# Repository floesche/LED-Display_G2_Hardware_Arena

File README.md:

---
title: Arena PCBs
parent: Generation 2
---

## Project content

```
├── arena_12_20
│   ├── gerber_v1
│   ├── gerber_v2
│   ├── pdf
│   └── svg
├── arena_12_20_top
│   └── gerber_v1
├── arena_mini
│   ├── gerber_v1
│   └── pdf
├── full
│   ├── 12-ring
│   └── 24-ring
├── mod
├── pdfs
├── planar_arena_8x
│   └── gerber_v0p1
└── planar_arena_8x_base
    ├── v0p1
    └── v0p2
```

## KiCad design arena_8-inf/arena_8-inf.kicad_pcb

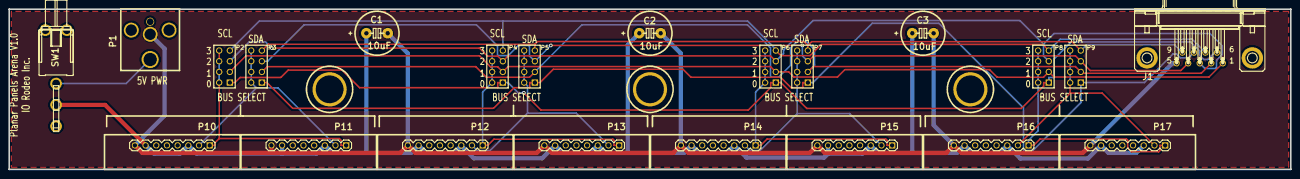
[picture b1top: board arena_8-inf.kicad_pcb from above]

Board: 2 copper layers, 304.8 x 38.1 mm, 25 parts (0 on the bottom side), 19 nets.

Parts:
C1, C2, C3: 10uF; JFRC_Capacitor_Polarized
J1: DB9; DB9_M09
M1, M2, M3: 1%2f4-20
P1: CONN_2; DCJACK_2PIN_HIGHCURRENT
P2, P3, P4, P5, P6, P7, P8, P9: CONN_4X2; pin_array_4x2
P10, P11, P12, P13, P14, P15, P16, P17: CONN_8; PANEL_RT_ANG_INV
SW1: SWITCH_INV; JFRC_LPV-1

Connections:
/5V: C1.1, C2.1, C3.1, P10.3, P10.7, P11.3, P11.7, P12.3, P12.7, P13.3, P13.7, P14.3, P14.7, P15.3, P15.7, P16.3, P16.7, P17.3, P17.7, SW1.2
/SCL0: J1.6, P2.1, P4.1, P6.1, P8.1
/SCL1: J1.1, P2.3, P4.3, P6.3, P8.3
/SCL2: J1.3, P2.5, P4.5, P6.5, P8.5
/SCL3: J1.7, P2.7, P4.7, P6.7, P8.7
/SCL_A: P2.2, P2.4, P2.6, P2.8, P10.1, P11.1
/SCL_B: P4.2, P4.4, P4.6, P4.8, P12.1, P13.1
/SCL_C: P6.2, P6.4, P6.6, P6.8, P14.1, P15.1
/SCL_D: P8.2, P8.4, P8.6, P8.8, P16.1, P17.1
/SDA0: J1.8, P3.1, P5.1, P7.1, P9.1
/SDA1: J1.2, P3.3, P5.3, P7.3, P9.3
/SDA2: J1.4, P3.5, P5.5, P7.5, P9.5
/SDA3: J1.9, P3.7, P5.7, P7.7, P9.7
/SDA_A: P3.2, P3.4, P3.6, P3.8, P10.2, P11.2
/SDA_B: P5.2, P5.4, P5.6, P5.8, P12.2, P13.2
/SDA_C: P7.2, P7.4, P7.6, P7.8, P14.2, P15.2
/SDA_D: P9.2, P9.4, P9.6, P9.8, P16.2, P17.2
GND: C1.2, C2.2, C3.2, J1.5, P1.2, P10.8, P11.8, P12.8, P13.8, P14.8, P15.8, P16.8, P17.8
unnamed: P1.1, SW1.1

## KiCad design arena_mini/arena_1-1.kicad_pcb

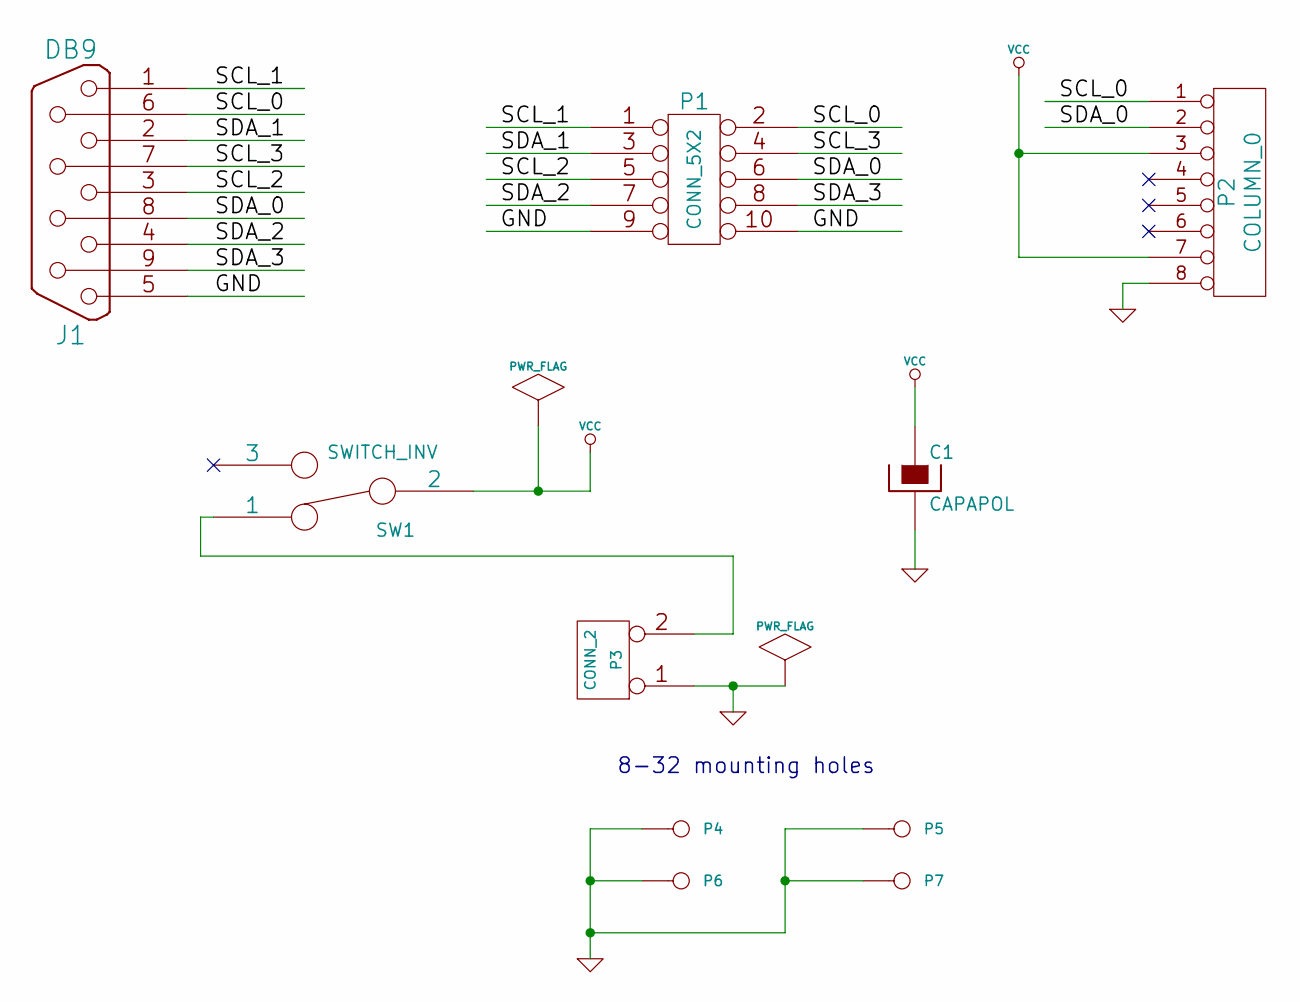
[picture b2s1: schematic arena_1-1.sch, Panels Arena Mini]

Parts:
C1: CAPAPOL
J1: DB9
P1: CONN_5X2
P2: COLUMN_0
P3: CONN_2
P4, P5, P6, P7: CONN_1
SW1: SWITCH_INV

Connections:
/GND: C1.2, J1.5, P1.9, P1.10, P2.8, P3.1, P4.1, P5.1, P6.1, P7.1
/SCL_0: J1.6, P1.2, P2.1
/SCL_1: J1.1, P1.1
/SCL_2: J1.3, P1.5
/SCL_3: J1.7, P1.4
/SDA_0: J1.8, P1.6, P2.2
/SDA_1: J1.2, P1.3
/SDA_2: J1.4, P1.7
/SDA_3: J1.9, P1.8
unnamed: P3.2 (PM), SW1.1
VCC: C1.1, P2.3, P2.7, SW1.2

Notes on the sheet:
8-32 mounting holes

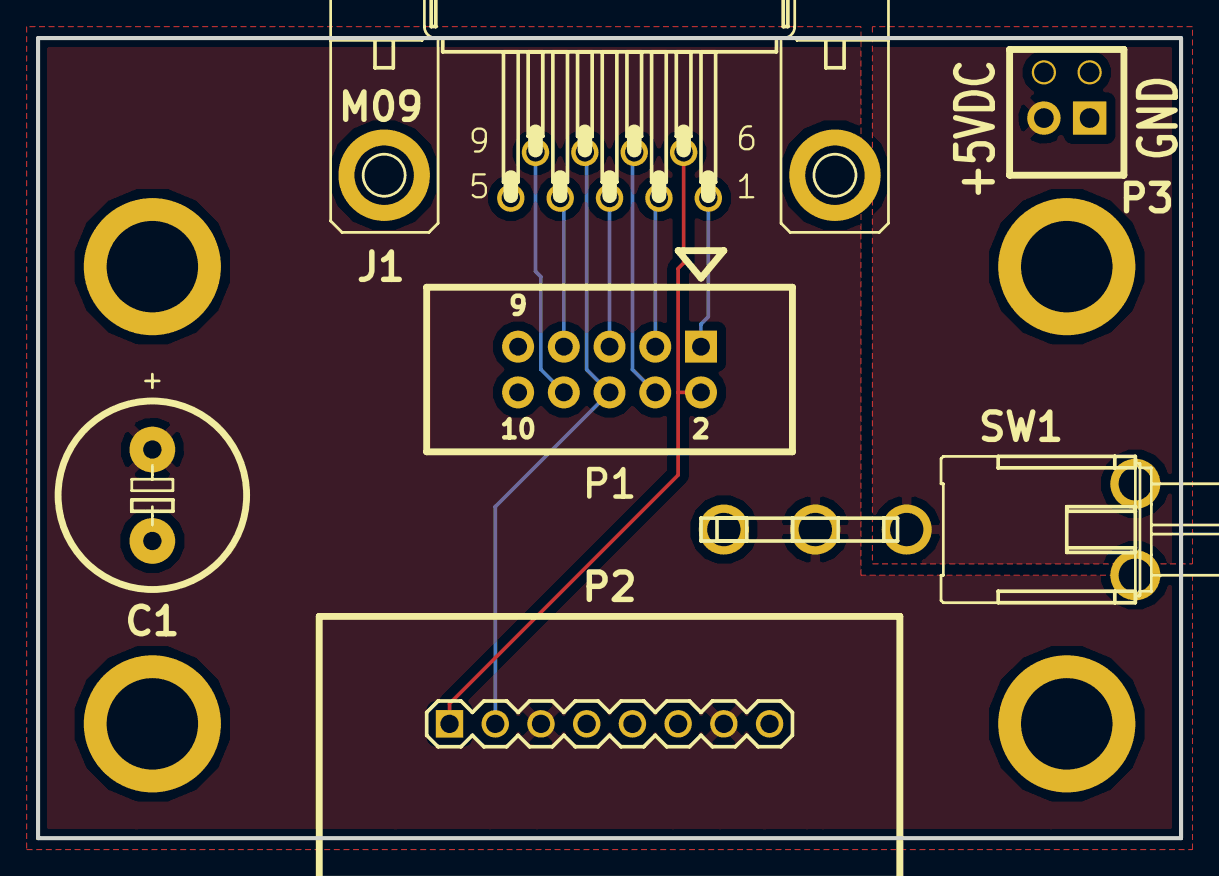
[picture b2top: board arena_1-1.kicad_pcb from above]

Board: 2 copper layers, 63.5 x 44.4 mm, 10 parts (0 on the bottom side), 11 nets.

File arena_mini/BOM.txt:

-*- mode:org -*-

# panels_arena_mini.lst
| ref | value      |
|-----+------------|
| C1  | CAPAPOL    |
| J1  | DB9        |
| P1  | CONN_5X2   |
| P2  | COLUMN_0   |
| P3  | CONN_2     |
| P4  | CONN_1     |
| P5  | CONN_1     |
| P6  | CONN_1     |
| P7  | CONN_1     |
| SW1 | SWITCH_INV |

# Bill of Materials
| ! | part  | description                                               | vendor       | part number   | quantity |  cost |
|---+-------+-----------------------------------------------------------+--------------+---------------+----------+-------|
|   | PCB   | panels_arena_mini 1.0                                     | protoexpress | 192719-INTJ   |        1 | 21.56 |
|   | C1    | CAP TANTALUM 10UF 25V 10% RAD                             | digikey      | 478-4170-ND   |        1 |  0.81 |
|   | J1    | CONN D-SUB PLUG R/A 9POS GOLD/FL                          | digikey      | A35113-ND     |        1 |  1.91 |
|   | P1    | CONN HEADER 2.54MM 10POS GOLD                             | digikey      | S9169-ND      |        1 |  0.31 |
|   | P2    | CONN RCPT .100" 8POS SNGL TIN                             | digikey      | SAM1222-08-ND |        1 |  1.67 |
|   | P3    | CONN TERM BLOCK 2.54MM 2POS                               | digikey      | 277-1273-ND   |        1 |  1.10 |
|   | P4-7  | SCREW MACHINE PHIL 8-32X3/8 SS                            | digikey      | H715-ND       |        4 |  0.12 |
|   | P4-7  | STANDOFF HEX 8-32THR ALUM .500"L                          | digikey      | 2217K-ND      |        4 |  0.45 |
|   | SW1   | SWITCH TOGGLE SPDT SEAL VERT R/A                          | digikey      | CKN1513-ND    |        1 |  6.93 |
|   |       | IDC Female 10 Position 2.54mm IDT Right Angle Cable Mount | jameco       | 525309        |        2 |  1.19 |
|   |       | CABLE 10 COND 5' GRAY RIBBON                              | digikey      | AE10G-5-ND    |        1 |  1.44 |
|---+-------+-----------------------------------------------------------+--------------+---------------+----------+-------|
| # | total |                                                           |              |               |          | 40.39 |
#+TBLFM: @13$7=(@I$quantity..@II$quantity)*(@I$cost..@II$cost);%.2f;N

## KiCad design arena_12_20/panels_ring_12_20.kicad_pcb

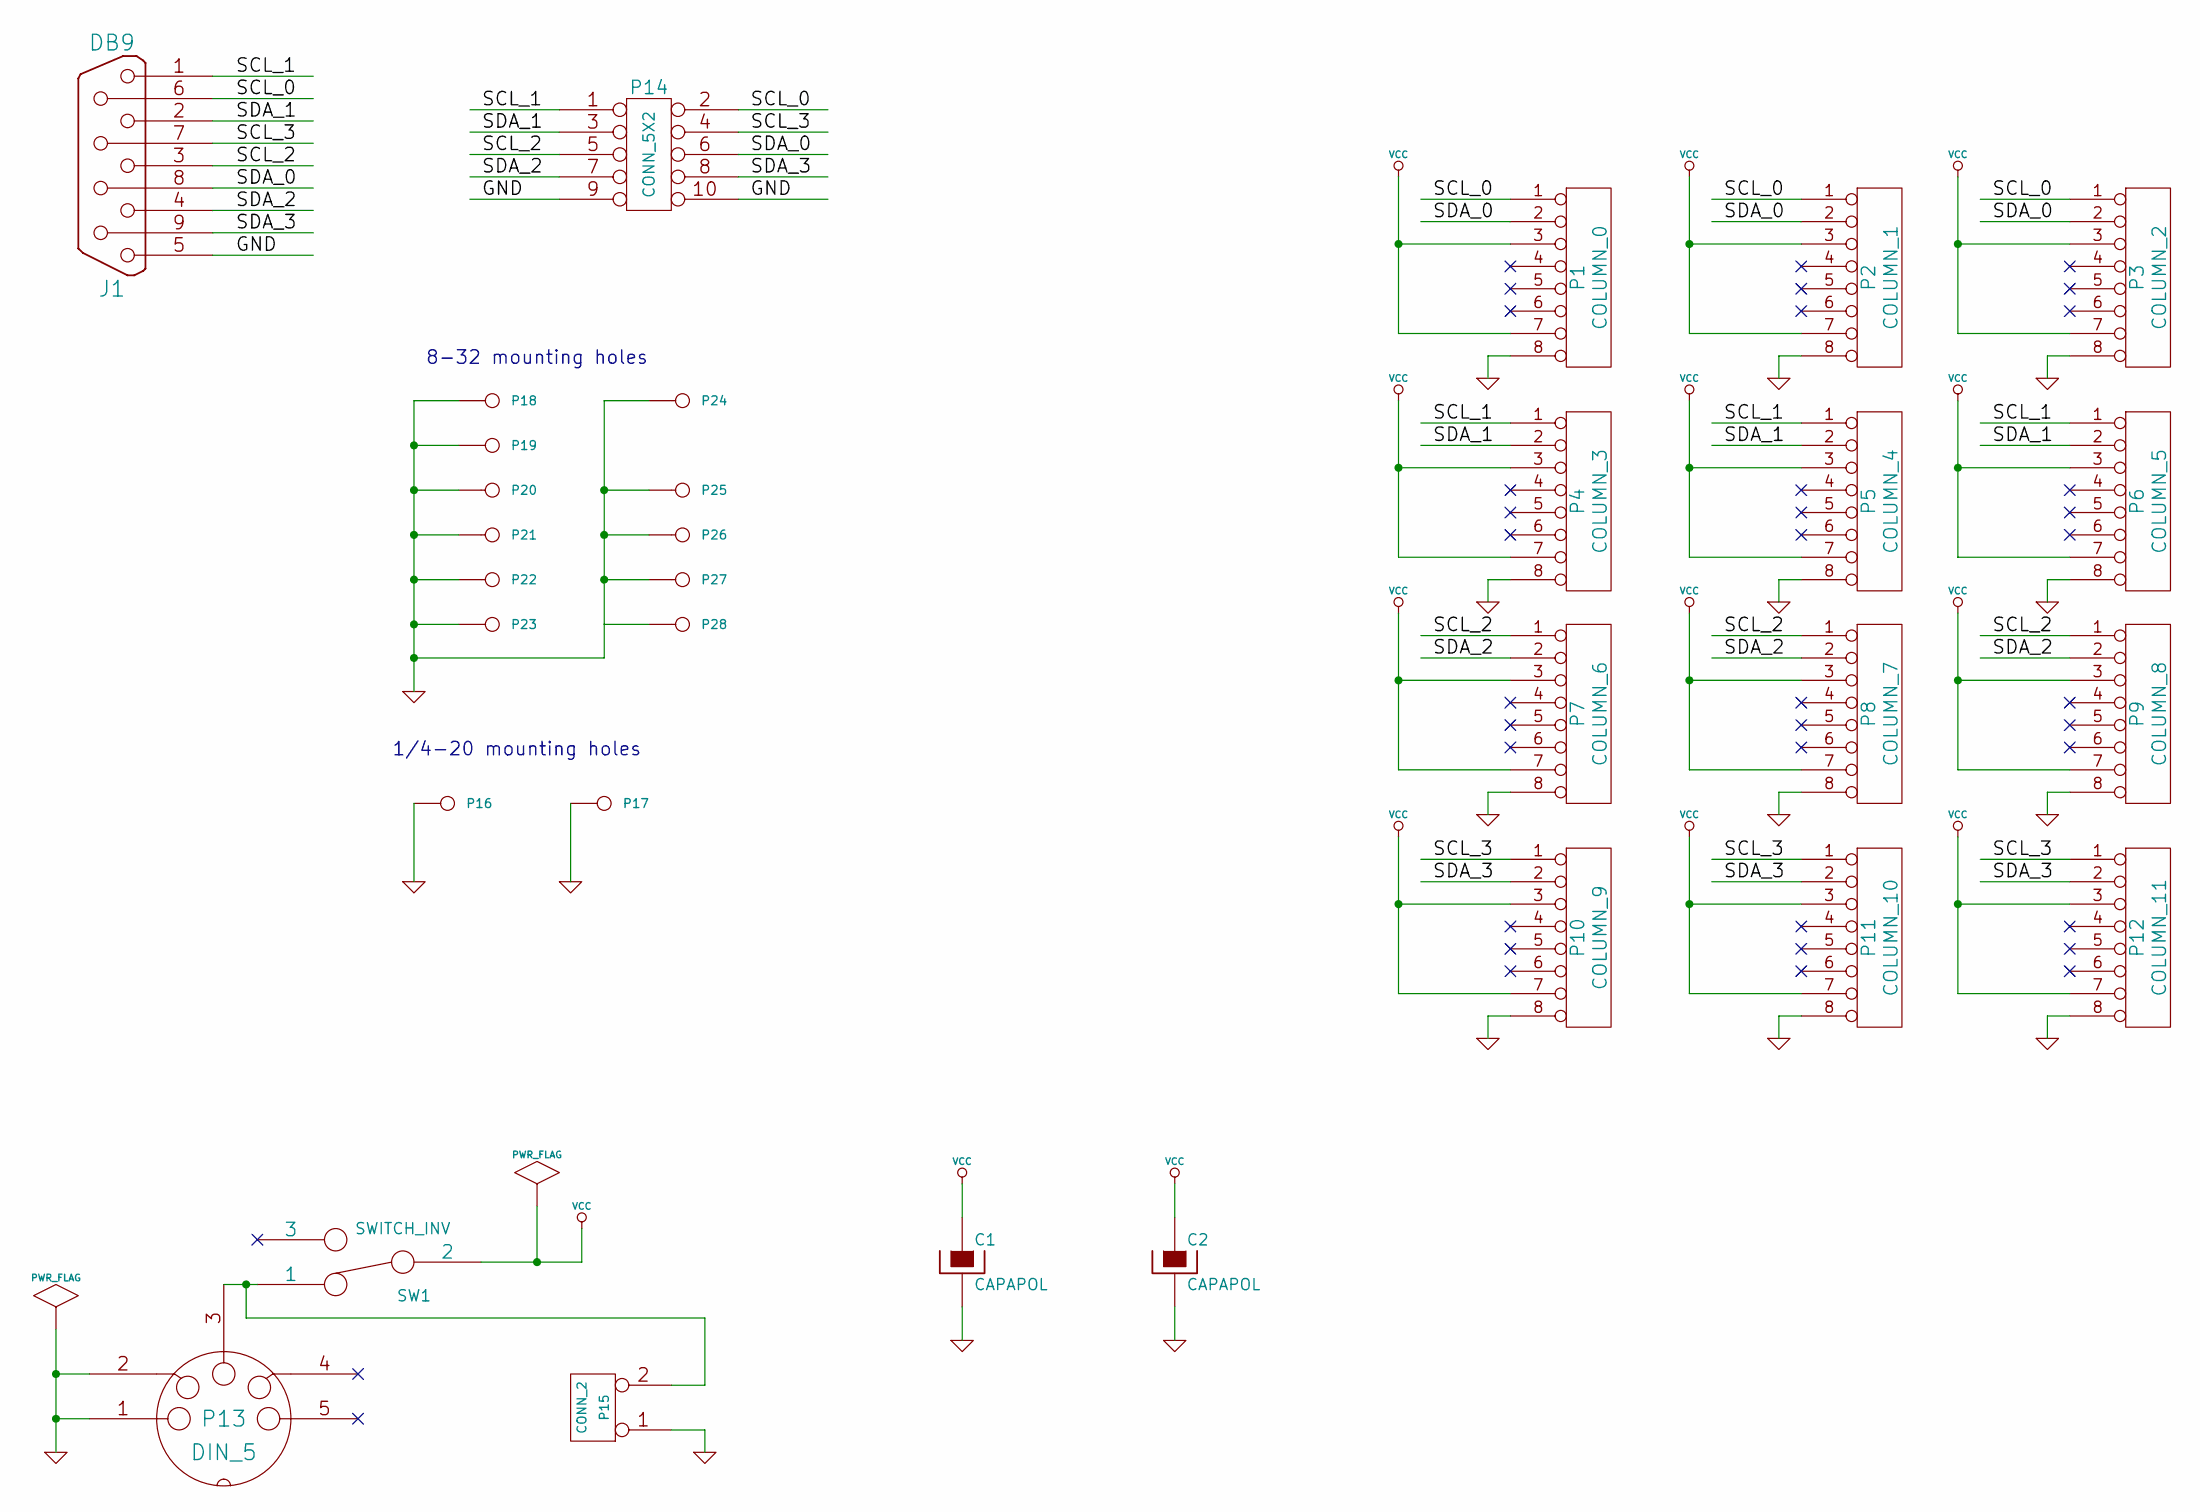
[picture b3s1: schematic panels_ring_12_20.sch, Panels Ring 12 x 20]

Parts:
C1, C2: CAPAPOL
J1: DB9
P1: COLUMN_0
P2: COLUMN_1
P3: COLUMN_2
P4: COLUMN_3
P5: COLUMN_4
P6: COLUMN_5
P7: COLUMN_6
P8: COLUMN_7
P9: COLUMN_8
P10: COLUMN_9
P11: COLUMN_10
P12: COLUMN_11
P13: DIN_5
P14: CONN_5X2
P15: CONN_2
P16, P17, P18, P19, P20, P21, P22, P23, P24, P25, P26, P27, P28: CONN_1
SW1: SWITCH_INV

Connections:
/SCL_0: J1.6, P1.1, P2.1, P3.1, P14.2
/SCL_1: J1.1, P4.1, P5.1, P6.1, P14.1
/SCL_2: J1.3, P7.1, P8.1, P9.1, P14.5
/SCL_3: J1.7, P10.1, P11.1, P12.1, P14.4
/SDA_0: J1.8, P1.2, P2.2, P3.2, P14.6
/SDA_1: J1.2, P4.2, P5.2, P6.2, P14.3
/SDA_2: J1.4, P7.2, P8.2, P9.2, P14.7
/SDA_3: J1.9, P10.2, P11.2, P12.2, P14.8
GND: C1.2, C2.2, J1.5, P1.8, P2.8, P3.8, P4.8, P5.8, P6.8, P7.8, P8.8, P9.8, P10.8, P11.8, P12.8, P13.1, P13.2, P14.9, P14.10, P15.1, P16.1, P17.1, P18.1, P19.1, P20.1, P21.1, P22.1, P23.1, P24.1, P25.1, P26.1, P27.1, P28.1
unnamed: P13.3, P15.2 (PM), SW1.1
VCC: C1.1, C2.1, P1.3, P1.7, P2.3, P2.7, P3.3, P3.7, P4.3, P4.7, P5.3, P5.7, P6.3, P6.7, P7.3, P7.7, P8.3, P8.7, P9.3, P9.7, P10.3, P10.7, P11.3, P11.7, P12.3, P12.7, SW1.2

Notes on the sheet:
1/4-20 mounting holes
8-32 mounting holes

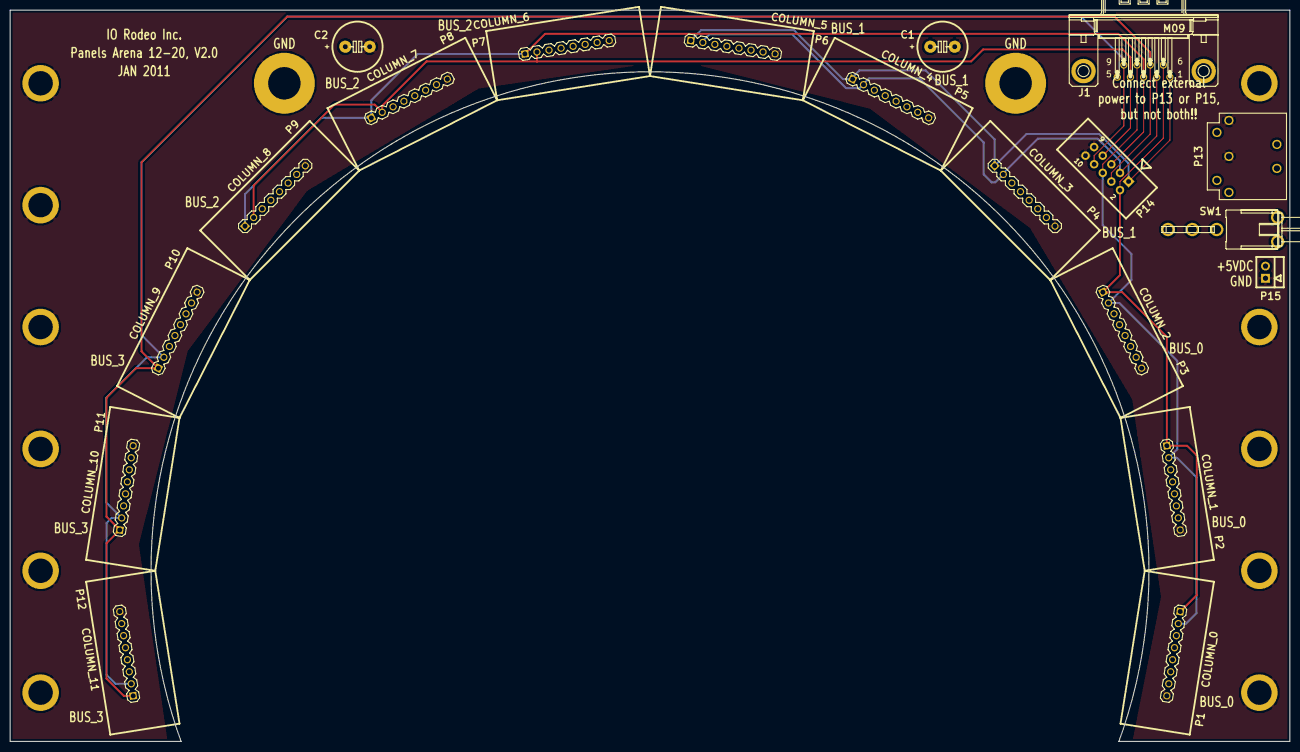
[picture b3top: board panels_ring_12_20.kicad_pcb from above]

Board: 4 copper layers, 266.7 x 152.4 mm, 32 parts (0 on the bottom side), 11 nets.

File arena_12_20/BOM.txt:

-*- mode:org -*-

# panels_ring_12_20.lst
| ref | value      |
|-----+------------|
| C1  | CAPAPOL    |
| C2  | CAPAPOL    |
| J1  | DB9        |
| P1  | COLUMN_0   |
| P2  | COLUMN_1   |
| P3  | COLUMN_2   |
| P4  | COLUMN_3   |
| P5  | COLUMN_4   |
| P6  | COLUMN_5   |
| P7  | COLUMN_6   |
| P8  | COLUMN_7   |
| P9  | COLUMN_8   |
| P10 | COLUMN_9   |
| P11 | COLUMN_10  |
| P12 | COLUMN_11  |
| P13 | DIN_5      |
| P14 | CONN_5X2   |
| P15 | CONN_2     |
| P16 | CONN_1     |
| P17 | CONN_1     |
| P18 | CONN_1     |
| P19 | CONN_1     |
| P20 | CONN_1     |
| P21 | CONN_1     |
| P22 | CONN_1     |
| P23 | CONN_1     |
| P24 | CONN_1     |
| P25 | CONN_1     |
| P26 | CONN_1     |
| P27 | CONN_1     |
| P28 | CONN_1     |
| SW1 | SWITCH_INV |

# Bill of Materials
| ! | part   | description                      | vendor       | part number   | quantity |   cost |
|---+--------+----------------------------------+--------------+---------------+----------+--------|
|   | PCB    | panels_arena_12-20 2.0           | protoexpress | 192373-IRW    |        1 |  74.13 |
|   | C1-2   | CAP TANTALUM 10UF 25V 10% RAD    | digikey      | 478-4170-ND   |        2 |   0.81 |
|   | J1     | CONN D-SUB PLUG R/A 9POS GOLD/FL | digikey      | A35113-ND     |        1 |   1.91 |
|   | P1-12  | CONN RCPT .100" 8POS SNGL TIN    | digikey      | SAM1222-08-ND |       12 |   1.67 |
|   | P13    | CONN DIN 5 PIN FEMALE PCB        | digikey      | CP-2350-ND    |        1 |   1.20 |
|   | P14    | CONN HEADER 2.54MM 10POS GOLD    | digikey      | S9169-ND      |        1 |   0.31 |
|   | P15    | CONN TERM BLOCK 2.54MM 2POS      | digikey      | 277-1273-ND   |        1 |   1.10 |
|   | P16-28 | SCREW MACHINE PHIL 8-32X3/8 SS   | digikey      | H715-ND       |       13 |   0.12 |
|   | P16-28 | STANDOFF HEX 8-32THR ALUM .500"L | digikey      | 2217K-ND      |       13 |   0.45 |
|   | SW1    | SWITCH TOGGLE SPDT SEAL VERT R/A | digikey      | CKN1513-ND    |        1 |   6.93 |
|---+--------+----------------------------------+--------------+---------------+----------+--------|
| # | total  |                                  |              |               |          | 114.65 |
#+TBLFM: @12$7=(@I$quantity..@II$quantity)*(@I$cost..@II$cost);%.2f;N

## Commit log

2010-12-28 Project creation.
2010-12-28 Modified board to put DIN5 connector on the left as per Gaby's suggestion.
2010-12-28 Re-routed board so that the db9, din5, switch and jumper are all on the left hand side of the board.
2010-12-29 Shortened the board a bit on Gaby's suggestion. Fixed some of the footprint modules so that the pads have solder mask etc.
2010-12-29 Created gerber and drill files for version 1.0 of the boards.
2010-12-29 Add top plate design for 12-20 arenas.
2010-12-29 Moved license file to top level directory.
2010-12-29 Swapped the power connector and power switch.
2010-12-29 Remade gerber files - to incorporate the latest changes.
2011-02-07 Version 2 redesign. Increased arena radius so panels will fit.
2011-02-07 Added arena_mini. Moved .mod file.
2011-02-08 Modified arena_mini board
2011-02-09 Finished Ver. 1 board design
2011-02-09 Finished Ver. 1 of panels_ring_12_20_top
2011-03-10 Added BOM
2011-03-11 Updated panels_arena_mini BOM
2011-03-22 Updated BOM. Parts may not be correct, just found similar components on digikey. Still waiting on official parts list.
2011-03-25 Updated BOM.
2011-04-06 Updated BOM
2012-11-01 Update part number for 12-20 top header.
2013-02-11 Minor changes.
2013-02-11 Added planar arena design.
2013-02-13 Added gerber files for planar arenas.
2013-02-13 Added design of planar arena base plate.
2013-02-28 Remade planar arena gerbers.
2013-02-28 Added gerber zip file for planar arena.
2013-08-07 Modified planar arena base.
2013-08-21 Added lower and upper support plates to planar arena base plate.
2014-03-11 Added .drl file to version 2.0 of 12_20 ring gerber files.
2014-03-27 Modified planar arena BOM.
2014-12-01 Added full arena designs.
2014-12-01 Renamed 12-ring eagle file sub-directory.
2014-12-01 Added pdf of 12 ring arena.
2014-12-01 Added some pdfs for quick access.
2014-12-31 Added zipped gerber files for easy ordering.
2020-08-06 getting ready for panel page
2021-11-10 move g2 documentation here
2021-11-10 resolve license conflict
    previously two licenses were provided: Apache 2.0 and CC-BY-1.0. Since
    this is primarily a hardware repository, we use CC-BY-4.0 from here on
    out.
2021-11-10 consistent file locations
2021-11-10 KiCAD cleanup
2021-11-10 more cleanup
2021-11-10 start documentation of arena
2021-11-10 consistent file renaming
2021-11-10 cleanup arena 12-20 top
2021-11-10 rename arena_12-20; optimize images
2021-11-10 cleanup arena 1-1
2021-11-10 rename arena_mini to arena_1-1
2021-11-10 cleanup arena_8-inf
2021-11-10 rename project folder
2021-11-10 add enclosure
2021-11-10 fix file naming
2021-11-10 integrate 24-24 arena
2021-11-10 cleanup arena description
2021-11-11 fix text
2021-11-12 split intro text into separate documents
2021-11-19 update links
2021-11-29 fix links
2021-11-29 md fixes
2021-11-30 consistent documentation
2022-05-20 add permalink
2022-12-12 add old user guide (work in progress from 2011)
